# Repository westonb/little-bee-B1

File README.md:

# Little Bee B1 - A high performance current & magnetic field probe
**Operating Instructions are located in the [getting-started](getting-started/README.md) folder**

The Little Bee B1 is an open source magnetic field and current probe based on an Anisotropic Magneto-Resistive (AMR) magnetic sensor.
It directly senses magnetic fields and measures current with a current sensing attachment consisting of a gapped ferrite toroid that is placed around a wire, establishing a fixed relation between the current in the wire and magnetic field the sensor is subject to.

The probe is capable of sensing DC currents and has a high frequency -3dB bandwidth in excess of 10Mhz. Typical specifications for current sensing are a +/- 5A range, and a 3mA RMS noise floor. For magnetic field sensing the probe has a +/- 6 gauss range. It is compatible with any 1M ohm input oscilloscope and is powered by a single AA battery. The probe uses a PIC microcontroller to automatically zero the sensor and to provide adjustable gain and bandwidth.

All project source files are in this repository and the project currently has a CrowdSupply [campaign](https://www.crowdsupply.com/weston-braun/little-bee)

### Typical Electrical Performance

#### Current sensing

- **Bandwidth**: DC - 10 MHz
- **Sensitivity**: 0.25 Volts/Amp
- **Max Current**: +/- 5 A
- **Noise**
    - 3 mA RMS at 10 MHz bandwidth
    - 2 mA RMS at 1 MHz bandwidth
- **DC Accuracy**: +/- 15%
- **Insertion Impedance**: 100 nH in parallel with 70 Ohms

#### Magnetic Field Sensing

- **Bandwidth**: DC - 10 MHz
- **Sensitivity**: 0.2 Volts/Gauss
- **Max Field**: +/- 6 Gauss
- **Noise**
    - 4mG RMS at 10 MHz bandwidth
    - 2.5mG RMS at 1 MHz bandwidth

## Operation
Connect the Little Bee to any oscilloscope with a SMA-BNC cable. When the probe is powered on it automatically zeros and starts in the high bandwidth and low gain mode. Tapping the "Mode Select" button will cycle through the bandwidth and gain options, which are indicated by the LED color.

The probe should be re-zeroed after switching modes. This is accomplished by pressing and holding the "zero/reset" button for at least one second before releasing. The LED will blink once when the button is first pressed and a second time when the zeroing operation is done.

When the sensor is exposed to an excessive magnetic field, or excessive current when the current sensing attachment is used, the sensor will be demagnetized and need to be reset for normal operation. For on axis fields the probe can detect this and will turn the indicator light red.
Off axis fields, which can occur when the probe is used for magnetic field sensing, can exceed the sensor limit without being detected. This will result a loss of sensitivity and noticeable distortion in the sensed waveforms.  
The sensor can be reset and normal operation restored without impacting the zeroing of the probe by tapping the "zero/reset" button, which will briefly flash the indicator light.

If the probe senses a low battery that will inhibit normal operation the indicator light will flash red. An alkaline AA battery should provide around 4 hours of battery life.

### Current Sensing
Current sensing is achieved with the current sensing attachment, which clips on to the tip of the probe. The current sensing attachment uses a ferrite core to translate the current flowing in to a wire into a known magnetic field strength.
A wire can be threaded through the current sensing attachment or the current sensing attachment can be slipped over a wire before being clipped on. With the logo and writing on the Little Bee facing the user, a wire carrying current away from the user will be read as a positive current.

The location of the wire within the current sensing attachment has some impact on the sensitivity of the probe due to the magnetic field in generates. It is recommended to keep the wire on the opposite side of the sensing tip within the aperture of the current sensing attachment.

For higher resolution when measuring low currents, multiple turns of the wire can be made through the aperture of the current sensing attachment. The final sensitivity will be the set sensitivity times the number of turns.

Tapping the "Mode Select" button will cycle through the bandwidth and gain options, which are indicated by the LED color:

| LED Color | Mode                    |
|-----------|-------------------------|
| Green     | 10MHz bandwidth 0.25V/A |
| Yellow    | 1MHz bandwidth 0.25V/A  |
| Blue      | 10MHz bandwidth 1V/A    |
| Teal      | 1MHz Bandwidth 1V/A     |

The gain of the probe can be adjusted with the labeled trimmer resistor on the PCB. Units are shipped calibrated to the above gains.

### Magnetic Field Sensing
The magnetic sensor is located approximately 1.0mm offset from the tip of the probe. The Little Bee will measure a magnetic field entering perpendicular to the top of the probe as a positive voltage. To measure the magnetic field emitted by a PCB trace the probe should be placed perpendicular to the PCB with the long direction of the tip parallel to the trace.

The earth's magnetic field is typically between 0.3 - 0.6 Gauss, depending on geographic location. This is well within the sensing range of the probe. Additionally, large ferrous objects and transformers can emit stray magnetic fields. It is recommended the Little Bee is zeroed while holding it in the orientation used for taking measurements to reduce the error introduced by stray magnetic fields.

The gain of the probe is calibrated based on measurements with the current sensing attachment, so the true sensitivity will depend on the tolerance current sensing attachment. The nominal sensitivities are:

| LED Color | Mode                           |
|-----------|--------------------------------|
| Green     | 10MHz bandwidth 0.2 V/Gauss  |
| Yellow    | 1MHz bandwidth 0.2 V/Gauss   |
| Blue      | 10MHz bandwidth 0.8 V/Gauss  |
| Teal      | 1MHz Bandwidth 0.8 V/Gauss   |

## Hardware
The kicad PCB files are in the [PCB](pcb/) directory and the [schematic](doc/current-sense.pdf) is in the doc directory.

## Firmware
The Little Bee uses a PIC16 microcontroller to automatically zero the probe and control gain and bandwidth switching. The firmware is built with the
MPLAB X IDE and the complete project is in the [firmware](firmware) directory

## Open Source
This work is licensed under a
[Creative Commons Attribution-ShareAlike 4.0 International License][cc-by-sa].

[![CC BY-SA 4.0][cc-by-sa-image]][cc-by-sa]

[cc-by-sa]: http://creativecommons.org/licenses/by-sa/4.0/
[cc-by-sa-image]: https://licensebuttons.net/l/by-sa/4.0/88x31.png
[cc-by-sa-shield]: https://img.shields.io/badge/License-CC%20BY--SA%204.0-lightgrey.svg

## Demos
### Sensing the AC line current into a switch-mode power supply

### Sensing the magnetic field from an inductor

### Example Waveforms
Yellow Waveform: Little Bee B1

Green Waveform: Tektronix CT-2 Current Transformer
#### Ramp

#### SinC

#### Square Wave (Low Current)

#### Noise Floor

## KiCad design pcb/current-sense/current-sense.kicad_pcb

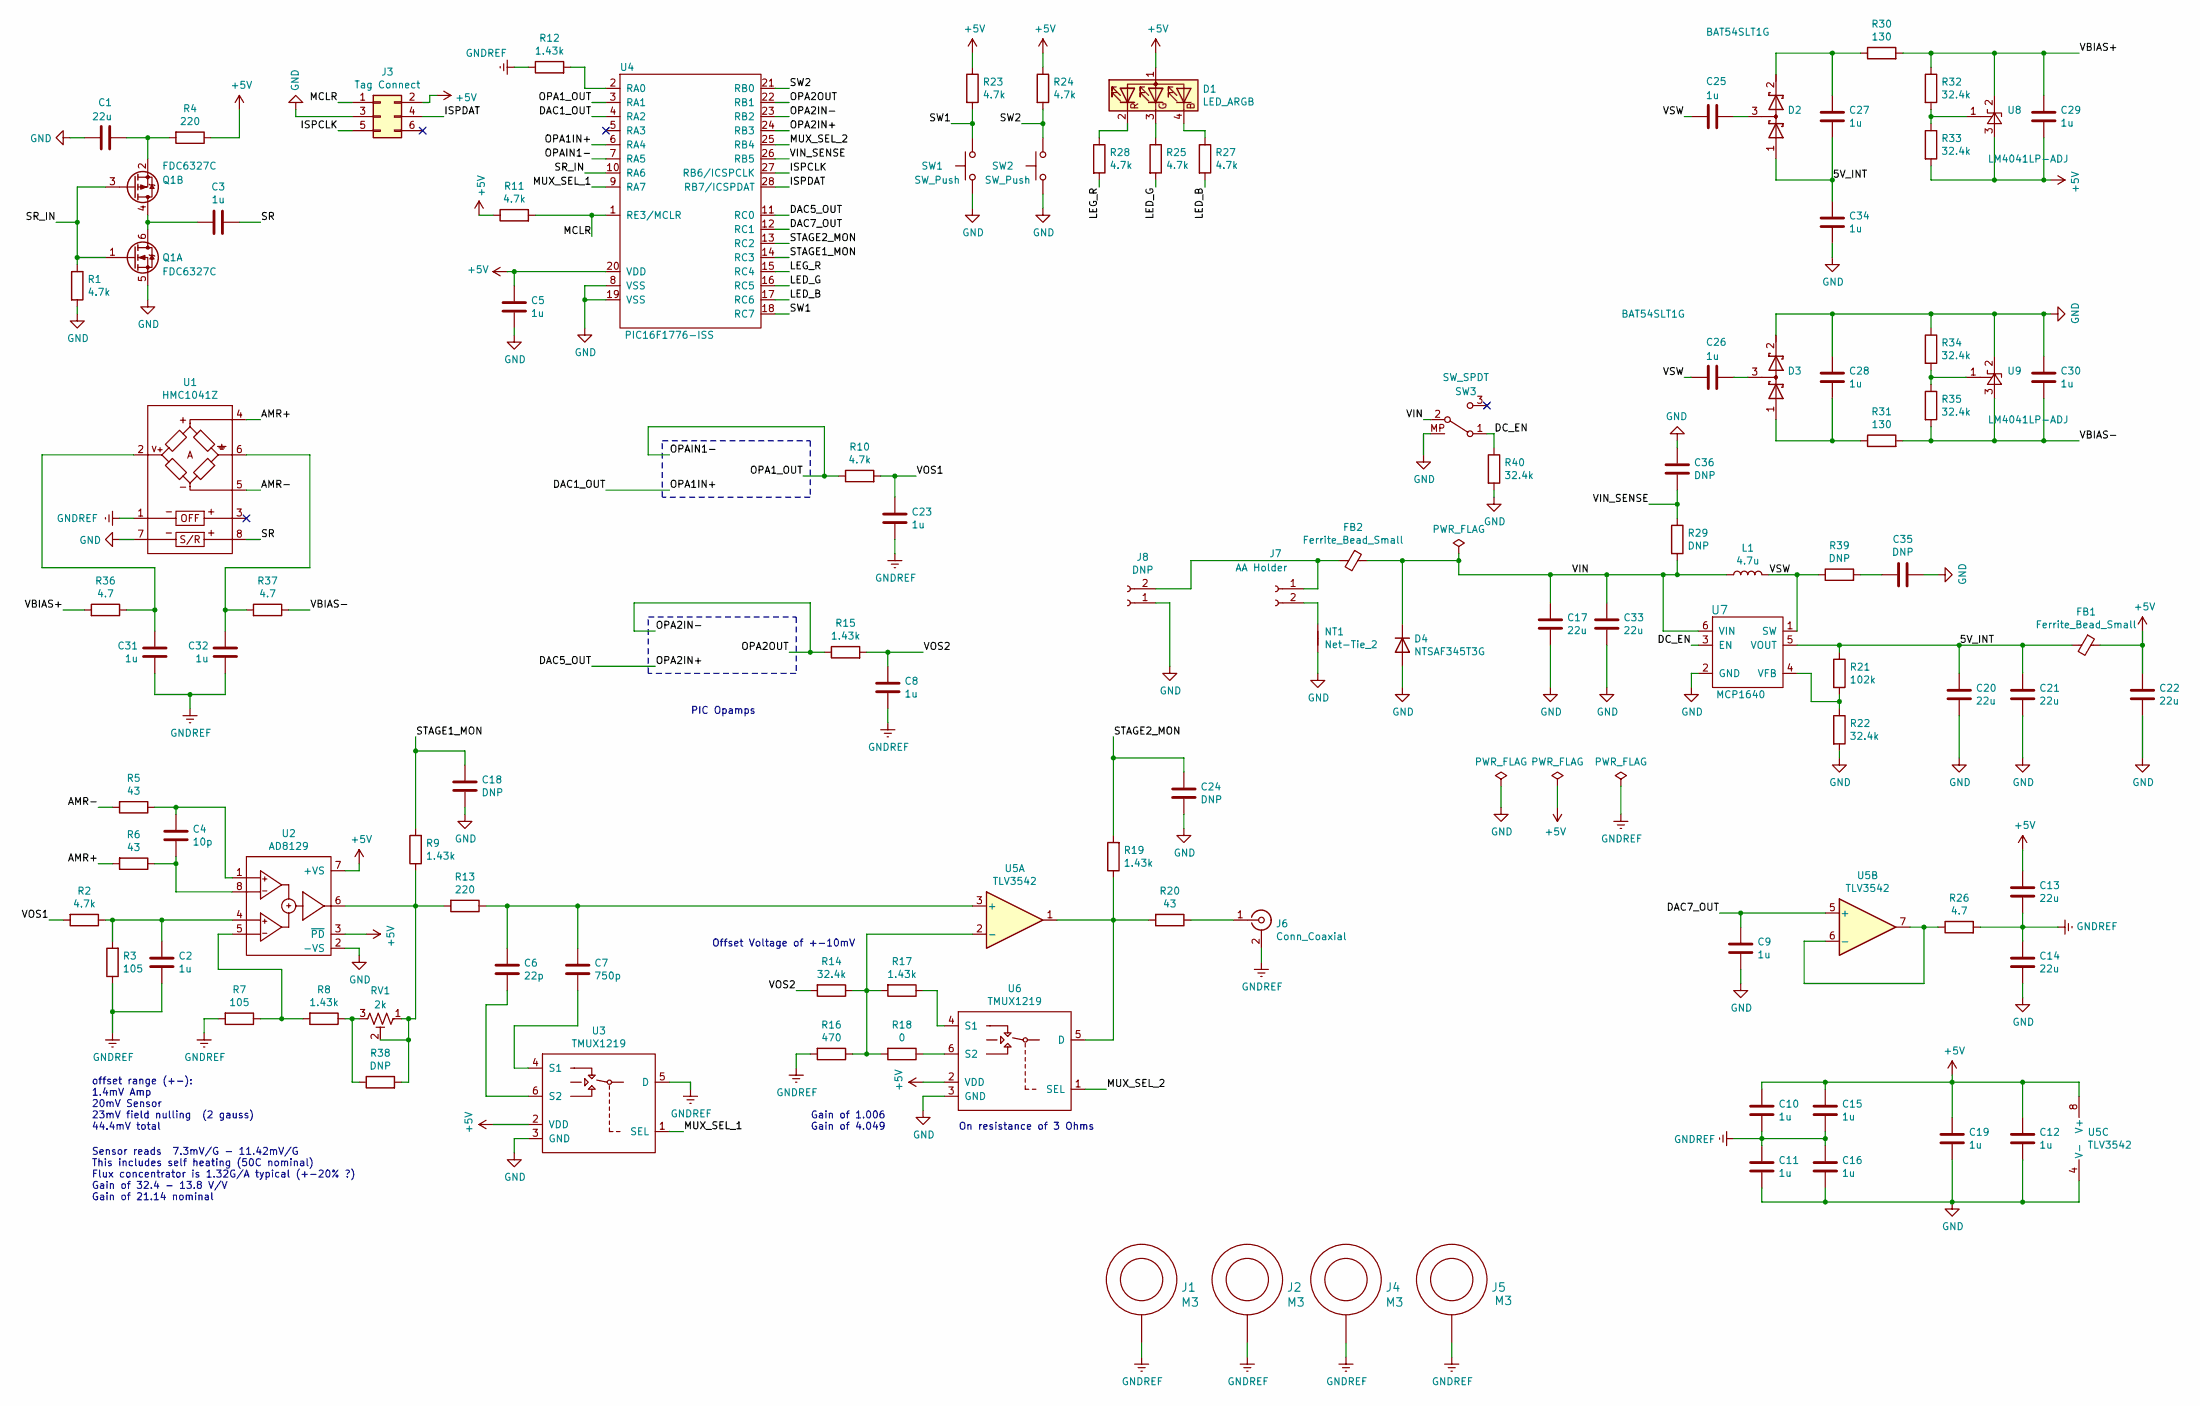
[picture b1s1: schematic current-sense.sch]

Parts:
C1, C13, C14, C17, C20, C21, C22, C33: 22u; C_0805_2012Metric; MPN LMK212BBJ226MG-T
C2, C3, C5, C8, C9, C10, C11, C12, C15, C16, C19, C23, C25, C26, C27, C28, C29, C30, C31, C32, C34: 1u; C_0603_1608Metric; MPN CL10B105KO8NNNC
C4: 10p; C_0603_1608Metric; MPN CL10C100CB8NNNC
C6: 22p; C_0603_1608Metric; MPN CL10C220JB8NFNC
C7: 750p; C_0603_1608Metric; MPN CC0603JRNPO9BN751
C18, C24, C35, C36: DNP; C_0603_1608Metric
D1: LED_ARGB; LED_Cree-PLCC4_2x2mm_CW; MPN CLMVC-FKA-CL1D1L71BB7C3C3
D2, D3: BAT54SLT1G; SOT-23; MPN BAT54SLT1G
D4: NTSAF345T3G; D_SMA; MPN NTSAF345T3G
FB1, FB2: Ferrite_Bead_Small; L_0805_2012Metric; MPN BKP2125HS600-T
J1, J2, J4, J5: M3; M3-tight-fit-socket-head
J3: Tag Connect; TC2030-IDC-NL
J6: Conn_Coaxial; SMA_Molex_73251-2200_Horizontal; MPN 619540-1
J7: AA Holder; AA-2460; MPN 2460
J8: DNP; JST_XH_B2B-XH-A_1x02_P2.50mm_Vertical; MPN B2B-XH-A(LF)(SN)
L1: 4.7u; L_VLCF4020; MPN VLCF4020T-4R7N1R2
NT1: Net-Tie_2; NET_TIE
Q1: FDC6327C; TSOT-23-6; MPN FDC6327C
R1, R2, R10, R11, R23, R24, R25, R27, R28: 4.7k; R_0603_1608Metric; MPN RC0603FR-074K7L
R3, R7: 105; R_0603_1608Metric; MPN RC0603FR-07105RL
R4, R13: 220; R_0603_1608Metric; MPN RC0603FR-07220RL
R5, R6, R20: 43; R_0603_1608Metric; MPN RC0603FR-0743RL
R8, R9, R12, R15, R17, R19: 1.43k; R_0603_1608Metric; MPN RC0603FR-071K43L
R14, R22, R32, R33, R34, R35, R40: 32.4k; R_0603_1608Metric; MPN RC0603FR-0732K4L
R16: 470; R_0603_1608Metric; MPN RC0603FR-07470RL
R18: 0; R_0603_1608Metric; MPN RC0603JR-070RL
R21: 102k; R_0603_1608Metric; MPN RMCF0603FT102K
R26, R36, R37: 4.7; R_0603_1608Metric; MPN RC0603FR-074R7L
R29, R38, R39: DNP; R_0603_1608Metric
R30, R31: 130; R_0603_1608Metric; MPN RC0603FR-07130RL
RV1: 2k; TRIMMER_PVG3A; MPN PVG3A202C01R00
SW1, SW2: SW_Push; SW_Tactile_SPST_Angled_PTS645Vx58-2LFS; MPN PTS645VL58-2 LFS
SW3: SW_SPDT; SW_EG1247_SPDT_Angled; MPN EG1247
U1: HMC1041Z; MPN HMC1041Z-TR
U2: AD8129; SOIC-8_3.9x4.9mm_P1.27mm; MPN AD8129ARZ
U3, U6: TMUX1219; SOT-363_SC-70-6; MPN TMUX1219DCKR
U4: PIC16F1776-ISS; SSOP-28_5.3x10.2mm_P0.65mm; MPN PIC16F1776-I/SS
U5: TLV3542; SOIC-8_3.9x4.9mm_P1.27mm; MPN TLV3542IDR
U7: MCP1640; SOT-23-6; MPN MCP1640BT-I/CHY
U8, U9: LM4041LP-ADJ; SOT-23; MPN LM4041CYM3-ADJ-TR

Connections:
+5V: C5.1, C10.1, C12.1, C13.1, C15.1, C19.1, C22.1, C29.2, D1.1 (A), FB1.1, J3.2, R4.1, R11.1, R23.1, R24.1, R33.2, U2.3 (~PD), U2.7 (+VS), U3.2 (VDD), U4.20 (VDD), U5.8 (V+), U6.2 (VDD), U8.3 (A)
/5V_INT: C20.1, C21.1, C27.2, C34.1, D2.1 (A), FB1.2, R21.1, U7.5 (VOUT)
/AMR+: R6.2, U1.4
/AMR-: R5.2, U1.5
/DAC1_OUT: U4.4 (RA2), U4.6 (RA4)
/DAC5_OUT: U4.11 (RC0), U4.24 (RB3)
/DAC7_OUT: C9.1, U4.12 (RC1), U5.5 (+)
/DC_EN: R40.1, SW3.1 (A), U7.3 (EN)
/ISPCLK: J3.5, U4.27 (RB6/ICSPCLK)
/ISPDAT: J3.4, U4.28 (RB7/ICSPDAT)
/LED_B: R27.2, U4.17 (RC6)
/LED_G: R25.2, U4.16 (RC5)
/LEG_R: R28.2, U4.15 (RC4)
/MCLR: J3.1, R11.2, U4.1 (RE3/MCLR)
/MUX_SEL_1: U3.1 (SEL), U4.9 (RA7)
/MUX_SEL_2: U4.25 (RB4), U6.1 (SEL)
/OPA1_OUT: R10.1, U4.3 (RA1), U4.7 (RA5)
/OPA2IN-: R15.1, U4.22 (RB1), U4.23 (RB2)
/SR: C3.2, U1.8
/SR_IN: Q1.1 (G), Q1.3 (G), R1.1, U4.10 (RA6)
/STAGE1_MON: C18.1, R9.2, U4.14 (RC3)
/STAGE2_MON: C24.1, R19.2, U4.13 (RC2)
/SW1: R23.2, SW1.1, U4.18 (RC7)
/SW2: R24.2, SW2.1, U4.21 (RB0)
/VBIAS+: C29.1, R30.2, R32.1, R36.2, U8.2 (K)
/VBIAS-: C30.2, R31.2, R35.2, R37.1, U9.3 (A)
/VIN: C17.1, C33.1, D4.1 (K), FB2.1, L1.1, R29.2, SW3.2 (B), U7.6 (VIN)
/VIN_SENSE: C36.2, R29.1, U4.26 (RB5)
/VOS1: C23.1, R2.2, R10.2
/VOS2: C8.1, R14.2, R15.2
/VSW: C25.2, C26.2, L1.2, R39.1, U7.1 (SW)
GND: C1.1, C5.2, C9.2, C11.2, C12.2, C14.2, C16.2, C17.2, C18.2, C19.2, C20.2, C21.2, C22.2, C24.2, C28.1, C30.1, C33.2, C34.2, C35.1, C36.1, D3.2 (K), D4.2 (A), J3.3, J8.1, NT1.2, Q1.5 (S), R1.2, R22.2, R34.1, R40.2, SW1.2, SW2.2, SW3.MP, U1.7, U2.2 (-VS), U3.3 (GND), U4.8 (VSS), U4.19 (VSS), U5.4 (V-), U6.3 (GND), U7.2 (GND), U9.2 (K)
GNDREF: C2.2, C8.2, C10.2, C11.1, C13.2, C14.1, C15.2, C16.1, C23.2, C31.2, C32.2, J1.1, J2.1, J4.1, J5.1, J6.2 (Ext), R3.1, R7.2, R12.1, R16.2, R26.2, U1.1, U3.5 (D)
unnamed: C1.2, Q1.2 (S), R4.2
unnamed: C2.1, R2.1, R3.2, U2.4
unnamed: C3.1, Q1.4 (D), Q1.6 (D)
unnamed: C4.1, R5.1, U2.1
unnamed: C4.2, R6.1, U2.8
unnamed: C6.1, C7.1, R13.1, U5.3 (+)
unnamed: C6.2, U3.6 (S2)
unnamed: C7.2, U3.4 (S1)
unnamed: C25.1, D2.3 (common)
unnamed: C26.1, D3.3 (common)
unnamed: C27.1, D2.2 (K), R30.1
unnamed: C28.2, D3.1 (A), R31.1
unnamed: C31.1, R36.1, U1.2
unnamed: C32.1, R37.2, U1.6
unnamed: C35.2, R39.2
unnamed: D1.2 (RK), R28.1
unnamed: D1.3 (GK), R25.1
unnamed: D1.4 (BK), R27.1
unnamed: FB2.2, J7.1, J8.2
unnamed: J6.1 (In), R20.1
unnamed: J7.2, NT1.1
unnamed: R7.1, R8.2, U2.5
unnamed: R12.2, U4.2 (RA0)
unnamed: R9.1, R13.2, R38.2, RV1.1, RV1.2, U2.6
unnamed: R14.1, R16.1, R17.2, R18.2, U5.2 (-)
unnamed: R17.1, U6.4 (S1)
unnamed: R18.1, U6.6 (S2)
unnamed: R19.1, R20.2, U5.1, U6.5 (D)
unnamed: R21.2, R22.1, U7.4 (VFB)
unnamed: R26.1, U5.6 (-), U5.7
unnamed: R32.2, R33.1, U8.1 (FB)
unnamed: R34.2, R35.1, U9.1 (FB)
unnamed: R8.1, R38.1, RV1.3

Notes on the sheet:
Gain of 1.006 Gain of 4.049
offset range (+-): 1.4mV Amp 20mV Sensor 23mV field nulling (2 gauss) 44.4mV total
Offset Voltage of +-10mV
Sensor reads 7.3mV/G - 11.42mV/G This includes self heating (50C nominal) Flux concentrator is 1.32G/A typical (+-20% ?) Gain of 32.4 - 13.8 V/V Gain of 21.14 nominal
On resistance of 3 Ohms
PIC Opamps

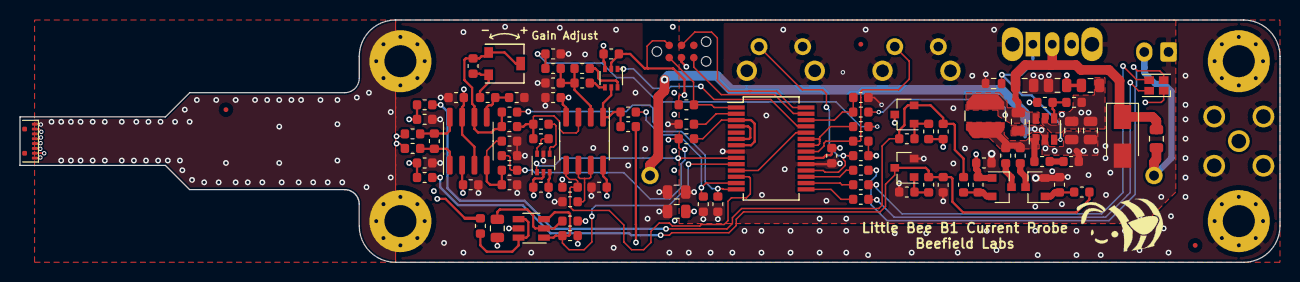
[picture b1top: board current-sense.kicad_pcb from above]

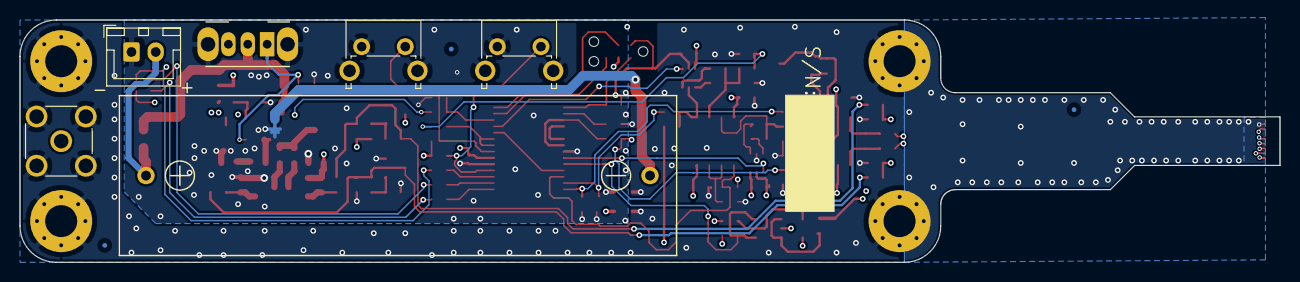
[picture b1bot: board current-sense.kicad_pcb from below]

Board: 4 copper layers, 130.0 x 25.0 mm, 106 parts (7 on the bottom side), 66 nets.

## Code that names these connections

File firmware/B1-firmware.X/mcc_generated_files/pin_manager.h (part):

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// get/set GNDREF_SENSE aliases
#define GNDREF_SENSE_TRIS                 TRISAbits.TRISA0
#define GNDREF_SENSE_LAT                  LATAbits.LATA0
#define GNDREF_SENSE_PORT                 PORTAbits.RA0
#define GNDREF_SENSE_WPU                  WPUAbits.WPUA0
#define GNDREF_SENSE_OD                   ODCONAbits.ODA0
#define GNDREF_SENSE_ANS                  ANSELAbits.ANSA0
#define GNDREF_SENSE_SetHigh()            do { LATAbits.LATA0 = 1; } while(0)
#define GNDREF_SENSE_SetLow()             do { LATAbits.LATA0 = 0; } while(0)
#define GNDREF_SENSE_Toggle()             do { LATAbits.LATA0 = ~LATAbits.LATA0; } while(0)
#define GNDREF_SENSE_GetValue()           PORTAbits.RA0
#define GNDREF_SENSE_SetDigitalInput()    do { TRISAbits.TRISA0 = 1; } while(0)
#define GNDREF_SENSE_SetDigitalOutput()   do { TRISAbits.TRISA0 = 0; } while(0)
#define GNDREF_SENSE_SetPullup()          do { WPUAbits.WPUA0 = 1; } while(0)
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#define RA1_SetHigh()            do { LATAbits.LATA1 = 1; } while(0)
#define RA1_SetLow()             do { LATAbits.LATA1 = 0; } while(0)
#define RA1_Toggle()             do { LATAbits.LATA1 = ~LATAbits.LATA1; } while(0)
#define RA1_GetValue()              PORTAbits.RA1
#define RA1_SetDigitalInput()    do { TRISAbits.TRISA1 = 1; } while(0)
#define RA1_SetDigitalOutput()   do { TRISAbits.TRISA1 = 0; } while(0)
#define RA1_SetPullup()             do { WPUAbits.WPUA1 = 1; } while(0)
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#define RA2_SetHigh()            do { LATAbits.LATA2 = 1; } while(0)
#define RA2_SetLow()             do { LATAbits.LATA2 = 0; } while(0)
#define RA2_Toggle()             do { LATAbits.LATA2 = ~LATAbits.LATA2; } while(0)
#define RA2_GetValue()              PORTAbits.RA2
#define RA2_SetDigitalInput()    do { TRISAbits.TRISA2 = 1; } while(0)
#define RA2_SetDigitalOutput()   do { TRISAbits.TRISA2 = 0; } while(0)
#define RA2_SetPullup()             do { WPUAbits.WPUA2 = 1; } while(0)
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#define RA4_SetHigh()            do { LATAbits.LATA4 = 1; } while(0)
#define RA4_SetLow()             do { LATAbits.LATA4 = 0; } while(0)
#define RA4_Toggle()             do { LATAbits.LATA4 = ~LATAbits.LATA4; } while(0)
#define RA4_GetValue()              PORTAbits.RA4
#define RA4_SetDigitalInput()    do { TRISAbits.TRISA4 = 1; } while(0)
#define RA4_SetDigitalOutput()   do { TRISAbits.TRISA4 = 0; } while(0)
#define RA4_SetPullup()             do { WPUAbits.WPUA4 = 1; } while(0)
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#define RA5_SetHigh()            do { LATAbits.LATA5 = 1; } while(0)
#define RA5_SetLow()             do { LATAbits.LATA5 = 0; } while(0)
#define RA5_Toggle()             do { LATAbits.LATA5 = ~LATAbits.LATA5; } while(0)
#define RA5_GetValue()              PORTAbits.RA5
#define RA5_SetDigitalInput()    do { TRISAbits.TRISA5 = 1; } while(0)
#define RA5_SetDigitalOutput()   do { TRISAbits.TRISA5 = 0; } while(0)
#define RA5_SetPullup()             do { WPUAbits.WPUA5 = 1; } while(0)
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// get/set SR aliases
#define SR_TRIS                 TRISAbits.TRISA6
#define SR_LAT                  LATAbits.LATA6
#define SR_PORT                 PORTAbits.RA6
#define SR_WPU                  WPUAbits.WPUA6
#define SR_OD                   ODCONAbits.ODA6
#define SR_SetHigh()            do { LATAbits.LATA6 = 1; } while(0)
#define SR_SetLow()             do { LATAbits.LATA6 = 0; } while(0)
#define SR_Toggle()             do { LATAbits.LATA6 = ~LATAbits.LATA6; } while(0)
#define SR_GetValue()           PORTAbits.RA6
#define SR_SetDigitalInput()    do { TRISAbits.TRISA6 = 1; } while(0)
#define SR_SetDigitalOutput()   do { TRISAbits.TRISA6 = 0; } while(0)
#define SR_SetPullup()          do { WPUAbits.WPUA6 = 1; } while(0)
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// get/set MUX_SEL1 aliases
#define MUX_SEL1_TRIS                 TRISAbits.TRISA7
#define MUX_SEL1_LAT                  LATAbits.LATA7
#define MUX_SEL1_PORT                 PORTAbits.RA7
#define MUX_SEL1_WPU                  WPUAbits.WPUA7
#define MUX_SEL1_OD                   ODCONAbits.ODA7
#define MUX_SEL1_SetHigh()            do { LATAbits.LATA7 = 1; } while(0)
#define MUX_SEL1_SetLow()             do { LATAbits.LATA7 = 0; } while(0)
#define MUX_SEL1_Toggle()             do { LATAbits.LATA7 = ~LATAbits.LATA7; } while(0)
#define MUX_SEL1_GetValue()           PORTAbits.RA7
#define MUX_SEL1_SetDigitalInput()    do { TRISAbits.TRISA7 = 1; } while(0)
#define MUX_SEL1_SetDigitalOutput()   do { TRISAbits.TRISA7 = 0; } while(0)
#define MUX_SEL1_SetPullup()          do { WPUAbits.WPUA7 = 1; } while(0)
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// get/set SW2 aliases
#define SW2_TRIS                 TRISBbits.TRISB0
#define SW2_LAT                  LATBbits.LATB0
#define SW2_PORT                 PORTBbits.RB0
#define SW2_WPU                  WPUBbits.WPUB0
#define SW2_ANS                  ANSELBbits.ANSB0
#define SW2_SetHigh()            do { LATBbits.LATB0 = 1; } while(0)
#define SW2_SetLow()             do { LATBbits.LATB0 = 0; } while(0)
#define SW2_Toggle()             do { LATBbits.LATB0 = ~LATBbits.LATB0; } while(0)
#define SW2_GetValue()           PORTBbits.RB0
#define SW2_SetDigitalInput()    do { TRISBbits.TRISB0 = 1; } while(0)
#define SW2_SetDigitalOutput()   do { TRISBbits.TRISB0 = 0; } while(0)
#define SW2_SetPullup()          do { WPUBbits.WPUB0 = 1; } while(0)
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#define RB1_SetHigh()            do { LATBbits.LATB1 = 1; } while(0)
#define RB1_SetLow()             do { LATBbits.LATB1 = 0; } while(0)
#define RB1_Toggle()             do { LATBbits.LATB1 = ~LATBbits.LATB1; } while(0)
#define RB1_GetValue()              PORTBbits.RB1
#define RB1_SetDigitalInput()    do { TRISBbits.TRISB1 = 1; } while(0)
#define RB1_SetDigitalOutput()   do { TRISBbits.TRISB1 = 0; } while(0)
#define RB1_SetPullup()             do { WPUBbits.WPUB1 = 1; } while(0)
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#define RB2_SetHigh()            do { LATBbits.LATB2 = 1; } while(0)
#define RB2_SetLow()             do { LATBbits.LATB2 = 0; } while(0)
#define RB2_Toggle()             do { LATBbits.LATB2 = ~LATBbits.LATB2; } while(0)
#define RB2_GetValue()              PORTBbits.RB2
#define RB2_SetDigitalInput()    do { TRISBbits.TRISB2 = 1; } while(0)
#define RB2_SetDigitalOutput()   do { TRISBbits.TRISB2 = 0; } while(0)
#define RB2_SetPullup()             do { WPUBbits.WPUB2 = 1; } while(0)
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#define RB3_SetHigh()            do { LATBbits.LATB3 = 1; } while(0)
#define RB3_SetLow()             do { LATBbits.LATB3 = 0; } while(0)
#define RB3_Toggle()             do { LATBbits.LATB3 = ~LATBbits.LATB3; } while(0)
#define RB3_GetValue()              PORTBbits.RB3
#define RB3_SetDigitalInput()    do { TRISBbits.TRISB3 = 1; } while(0)
#define RB3_SetDigitalOutput()   do { TRISBbits.TRISB3 = 0; } while(0)
#define RB3_SetPullup()             do { WPUBbits.WPUB3 = 1; } while(0)
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// get/set MUX_SEL2 aliases
#define MUX_SEL2_TRIS                 TRISBbits.TRISB4
#define MUX_SEL2_LAT                  LATBbits.LATB4
#define MUX_SEL2_PORT                 PORTBbits.RB4
#define MUX_SEL2_WPU                  WPUBbits.WPUB4
#define MUX_SEL2_OD                   ODCONBbits.ODB4
#define MUX_SEL2_ANS                  ANSELBbits.ANSB4
#define MUX_SEL2_SetHigh()            do { LATBbits.LATB4 = 1; } while(0)
#define MUX_SEL2_SetLow()             do { LATBbits.LATB4 = 0; } while(0)
#define MUX_SEL2_Toggle()             do { LATBbits.LATB4 = ~LATBbits.LATB4; } while(0)
#define MUX_SEL2_GetValue()           PORTBbits.RB4
#define MUX_SEL2_SetDigitalInput()    do { TRISBbits.TRISB4 = 1; } while(0)
#define MUX_SEL2_SetDigitalOutput()   do { TRISBbits.TRISB4 = 0; } while(0)
#define MUX_SEL2_SetPullup()          do { WPUBbits.WPUB4 = 1; } while(0)
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// get/set VIN_SENSE aliases
#define VIN_SENSE_TRIS                 TRISBbits.TRISB5
#define VIN_SENSE_LAT                  LATBbits.LATB5
#define VIN_SENSE_PORT                 PORTBbits.RB5
#define VIN_SENSE_WPU                  WPUBbits.WPUB5
#define VIN_SENSE_OD                   ODCONBbits.ODB5
#define VIN_SENSE_ANS                  ANSELBbits.ANSB5
#define VIN_SENSE_SetHigh()            do { LATBbits.LATB5 = 1; } while(0)
#define VIN_SENSE_SetLow()             do { LATBbits.LATB5 = 0; } while(0)
#define VIN_SENSE_Toggle()             do { LATBbits.LATB5 = ~LATBbits.LATB5; } while(0)
#define VIN_SENSE_GetValue()           PORTBbits.RB5
#define VIN_SENSE_SetDigitalInput()    do { TRISBbits.TRISB5 = 1; } while(0)
#define VIN_SENSE_SetDigitalOutput()   do { TRISBbits.TRISB5 = 0; } while(0)
#define VIN_SENSE_SetPullup()          do { WPUBbits.WPUB5 = 1; } while(0)
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#define RC0_SetHigh()            do { LATCbits.LATC0 = 1; } while(0)
#define RC0_SetLow()             do { LATCbits.LATC0 = 0; } while(0)
#define RC0_Toggle()             do { LATCbits.LATC0 = ~LATCbits.LATC0; } while(0)
#define RC0_GetValue()              PORTCbits.RC0
#define RC0_SetDigitalInput()    do { TRISCbits.TRISC0 = 1; } while(0)
#define RC0_SetDigitalOutput()   do { TRISCbits.TRISC0 = 0; } while(0)
#define RC0_SetPullup()             do { WPUCbits.WPUC0 = 1; } while(0)
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#define RC1_SetHigh()            do { LATCbits.LATC1 = 1; } while(0)
#define RC1_SetLow()             do { LATCbits.LATC1 = 0; } while(0)
#define RC1_Toggle()             do { LATCbits.LATC1 = ~LATCbits.LATC1; } while(0)
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
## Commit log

2020-12-11 first release candidate
2020-12-11 added simulation files
2020-12-11 added BOM
2020-12-11 changes to gain resistors
2020-12-11 added image files
2020-12-11 updated image
2020-12-12 added square wave waveform
2020-12-12 Initial readme file
2020-12-12 Create LICENSE
2021-01-25 added magnetics modeling files
2021-02-01 pre-production PCB assembly
2021-02-01 updated gerbers and PDF schematic
2021-03-04 added plots for magnetic modeling
2021-03-04 PCB MCAD Export
2021-04-10 production PCB version
2021-06-06 refactored auto-zero code and added absolute field sense mode
2021-06-14 production firmware with improved auto zero
2021-06-29 added production test data and getting started placeholder
2021-08-05 added operatig instructions
2023-04-03 updated documentation on mechanical assembly

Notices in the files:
firmware/B1-firmware.X/mcc_generated_files/pin_manager.h:
(c) 2018 Microchip Technology Inc. and its subsidiaries.
